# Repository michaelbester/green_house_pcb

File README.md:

This is the PCB design for the green house controller.  I used Kicad 6 to design the schematic and layout the board.

The uC pins connected to the fan #2, misc, and vent relays where incorrect.  
I jumpered these pins to unused pins that had output capability, but I can't get the outputs to go high.

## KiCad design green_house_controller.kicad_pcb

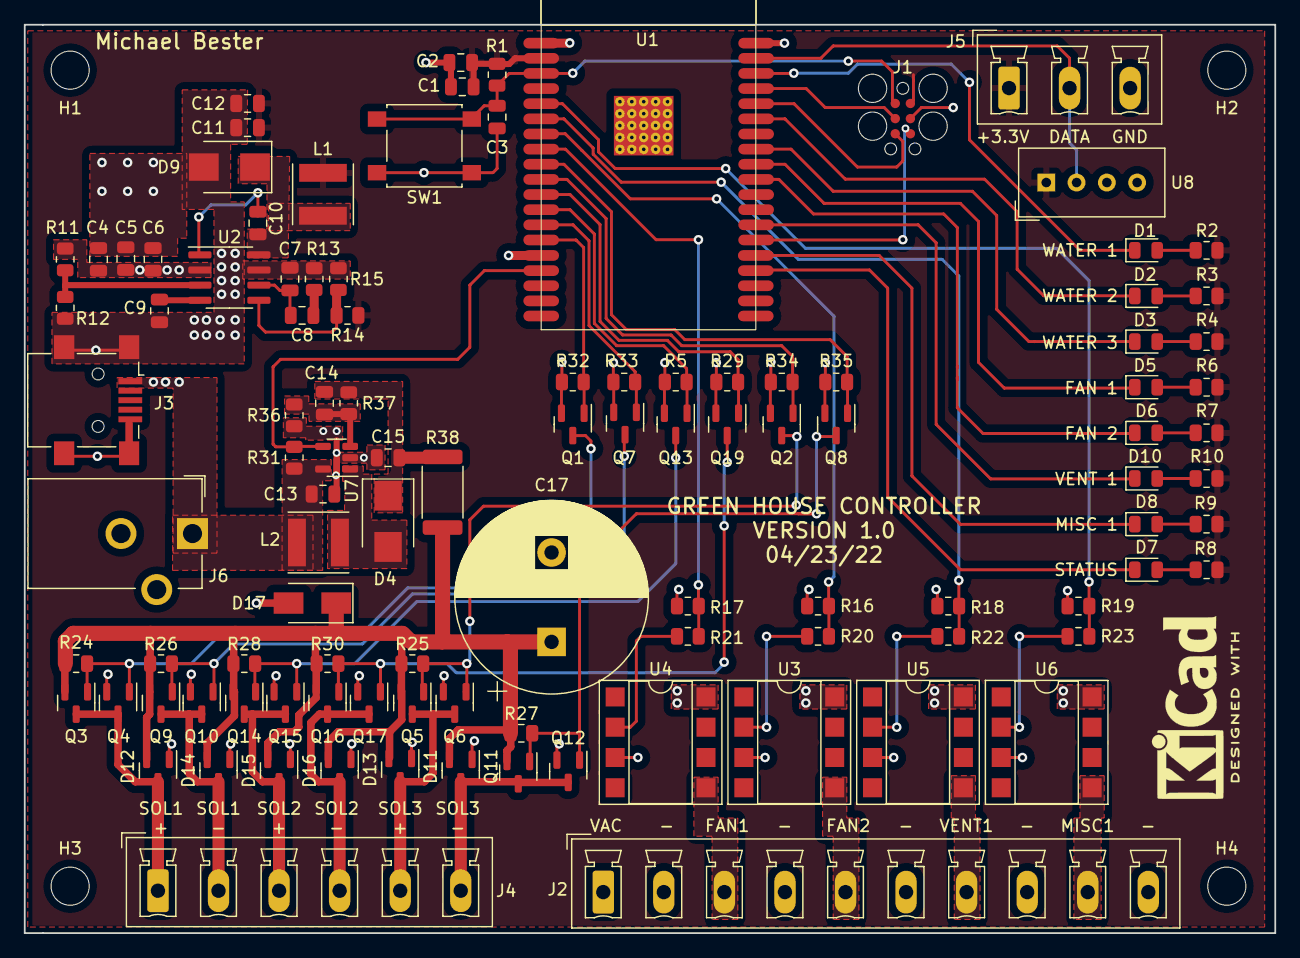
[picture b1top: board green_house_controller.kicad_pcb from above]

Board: 2 copper layers, 104.9 x 76.2 mm, 110 parts (0 on the bottom side), 68 nets.

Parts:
C1, C10: 0.1uF; C_0805_2012Metric
C2: 10uF; C_0805_2012Metric
C3: 1uF; C_0805_2012Metric
C4, C5, C15: 4.7uF; C_0805_2012Metric
C6: 0.01uF; C_0805_2012Metric
C7: 47pF; C_0805_2012Metric
C8: 1nF; C_0805_2012Metric
C9: 15nF; C_0805_2012Metric
C11, C12: 47uF; C_0805_2012Metric
C13: 2.2uF; C_0805_2012Metric
C14: 220pF; C_0805_2012Metric
C17: 2200uF; CP_Radial_D16.0mm_P7.50mm
D1: SOL_1; LED_0805_2012Metric
D2: SOL_2; LED_0805_2012Metric
D3: SOL_3; LED_0805_2012Metric
D4, D9: B240; D_SMB
D5: FAN; LED_0805_2012Metric
D6: VENT; LED_0805_2012Metric
D7: STATUS; LED_0805_2012Metric
D8: MISC_1; LED_0805_2012Metric
D10: VENT_1; LED_0805_2012Metric
D11, D12, D13, D14, D15, D16: BAT54S; SOT-23
D17: B140-E3; D_SMA
H1, H2, H3, H4: MountingHole; MountingHole_3.2mm_M3
J1: TC2030-IDC
J2: Screw_Terminal_01x10; PhoenixContact_MCV_1,5_10-G-5.08_1x10_P5.08mm_Vertical
J3: USB_B_Mini; USB_Mini-B_Lumberg_2486_01_Horizontal
J4: Screw_Terminal_01x06; PhoenixContact_MCV_1,5_6-G-5.08_1x06_P5.08mm_Vertical
J5: Screw_Terminal_01x03; PhoenixContact_MCV_1,5_3-G-5.08_1x03_P5.08mm_Vertical
J6: Barrel_Jack; BarrelJack_CUI_PJ-102AH_Horizontal
L1, L2: 10uH; L_Taiyo-Yuden_NR-50xx
Q1, Q2, Q7, Q8, Q13, Q19: 2N7002; SOT-23
Q3, Q5, Q9, Q11, Q14, Q16: DMP3068L; SOT-23
Q4, Q6, Q10, Q12, Q15, Q17: DMG3406L; SOT-23
R1, R12, R16, R17, R18, R19: 10K; R_0805_2012Metric
R2, R3, R4, R6, R7, R8, R9, R10: 330; R_0805_2012Metric
R5, R24, R25, R26, R27, R28, R29, R30, R32, R33, R34, R35, R36: 1K; R_0805_2012Metric
R11: 22K; R_0805_2012Metric
R13: 29.4K; R_0805_2012Metric
R14: 10.2K; R_0805_2012Metric
R15: 3.24K; R_0805_2012Metric
R20, R21, R22, R23: 200; R_0805_2012Metric
R31: 51K; R_0805_2012Metric
R37: 18.7K; R_0805_2012Metric
R38: 100; R_2512_6332Metric
SW1: SW_Push; SW_SPST_B3S-1000
U1: ESP32-WROVER
U2: TPS54231; SOIC-8_3.9x4.9mm_P1.27mm
U3, U4, U5, U6: TLP3825TP1_F; DIP-8_W7.62mm_SMDSocket_SmallPads
U7: LM2733XMF; SOT-23-5
U8: DHT11; Aosong_DHT11_5.5x12.0_P2.54mm

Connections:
+3V3: C1.1, C2.1, C11.1, C12.1, J1.2 (SWDIO), J5.1, L1.2, R1.1, R2.1, R3.1, R4.1, R6.1, R7.1, R8.1, R9.1, R10.1, R14.1, U1.2 (3V3), U8.1 (VCC)
+24V: C14.2, C15.1, D4.1 (K), R37.2, R38.1
+VDC: C17.1, D11.2, D12.2, D13.2, D14.2, D15.2, D16.2, D17.1 (K), Q3.2 (S), Q5.2 (S), Q9.2 (S), Q11.2 (S), Q14.2 (S), Q16.2 (S), R24.1, R25.1, R26.1, R27.1, R28.1, R30.1, R38.2
/microcontroller/BOOT_MODE: J1.6 (SWO), U1.25 (IO0)
/microcontroller/DHT11_DATA: J5.2, U1.37 (IO23), U8.2 (IO)
/microcontroller/EN_24V: R31.2, U1.16 (IO13), U7.4 (EN)
/microcontroller/ESP32_RX: J1.5 (GND), U1.34 (RXD0)
/microcontroller/ESP32_TX: J1.3 (NRESET), U1.35 (TXD0)
/microcontroller/FAN_1_CTRL: R17.1, R21.2, U1.8 (IO32_XTAL_32K_P)
/microcontroller/FAN_2_CTRL: R16.1, R20.2, U1.7 (IO35)
/microcontroller/LED_FAN_1: D5.1 (K), U1.30 (IO18)
/microcontroller/LED_FAN_2: D6.1 (K), U1.29 (IO5)
/microcontroller/LED_MISC_1: D8.1 (K), U1.24 (IO2)
/microcontroller/LED_SOL_1: D1.1 (K), U1.36 (IO22)
/microcontroller/LED_SOL_2: D2.1 (K), U1.33 (IO21)
/microcontroller/LED_SOL_3: D3.1 (K), U1.31 (IO19)
/microcontroller/LED_STATUS: D7.1 (K), U1.23 (IO15)
/microcontroller/LED_VENT_1: D10.1 (K), U1.26 (IO4)
/microcontroller/MISC_1_CTRL: R19.1, R23.2, U1.5 (SENSOR_VN_IO39)
/microcontroller/RESET: C3.1, J1.1 (VCC), R1.2, SW1.2, U1.3 (EN)
/microcontroller/SOL_1_CLOSE_CTRL: Q1.1 (G), R32.1, U1.14 (IO12)
/microcontroller/SOL_1_OPEN_CTRL: Q7.1 (G), R33.1, U1.13 (IO14)
/microcontroller/SOL_2_CLOSE_CTRL: Q13.1 (G), R5.1, U1.12 (IO27)
/microcontroller/SOL_2_OPEN_CTRL: Q19.1 (G), R29.1, U1.11 (IO26)
/microcontroller/SOL_3_CLOSE_CTRL: Q2.1 (G), R34.1, U1.10 (IO25)
/microcontroller/SOL_3_OPEN_CTRL: Q8.1 (G), R35.1, U1.9 (IO33_XTAL_32K_N)
/microcontroller/VENT_1_CTRL: R18.1, R22.2, U1.6 (IO34)
/power supply/VIN: C4.1, C5.1, C6.1, C13.1, J3.1 (VBUS), J6.1, L2.1, R11.1, R31.1, U2.2 (VIN), U7.5 (VIN)
/relay control/110VAC: J2.1, U3.8 (DRAIN), U4.8 (DRAIN), U5.8 (DRAIN), U6.8 (DRAIN)
/relay control/FAN_1_PWR: J2.3, U4.5 (DRAIN)
/relay control/FAN_2_PWR: J2.5, U3.5 (DRAIN)
/relay control/MISC_1_PWR: J2.9, U6.5 (DRAIN)
/relay control/VENT_1_PWR: J2.7, U5.5 (DRAIN)
/solenoid control/SOL_1_PWR+: D12.3, J4.1, Q3.3 (D), Q4.3 (D)
/solenoid control/SOL_1_PWR-: D14.3, J4.2, Q9.3 (D), Q10.3 (D)
/solenoid control/SOL_2_PWR+: D15.3, J4.3, Q14.3 (D), Q15.3 (D)
/solenoid control/SOL_2_PWR-: D16.3, J4.4, Q16.3 (D), Q17.3 (D)
/solenoid control/SOL_3_PWR+: D11.3, J4.5, Q5.3 (D), Q6.3 (D)
/solenoid control/SOL_3_PWR-: D13.3, J4.6, Q11.3 (D), Q12.3 (D)
Earth: J2.2, J2.4, J2.6, J2.8, J2.10
GND: C1.2, C2.2, C3.2, C4.2, C5.2, C6.2, C7.2, C9.2, C11.2, C12.2, C13.2, C15.2, C17.2, D9.2 (A), D11.1, D12.1, D13.1, D14.1, D15.1, D16.1, D17.2 (A), J1.4 (SWCLK), J3.5 (GND), J3.6 (Shield), J5.3, J6.2, Q1.2 (S), Q2.2 (S), Q4.2 (S), Q6.2 (S), Q7.2 (S), Q8.2 (S), Q10.2 (S), Q12.2 (S), Q13.2 (S), Q15.2 (S), Q17.2 (S), Q19.2 (S), R5.2, R12.2, R13.2, R15.2, R16.2, R17.2, R18.2, R19.2, R29.2, R32.2, R33.2, R34.2, R35.2, R36.1, SW1.1, U1.1 (GND), U1.15 (GND), U1.38 (GND), U1.39 (GND), U2.7 (GND), U3.3 (CATHODE), U4.3 (CATHODE), U5.3 (CATHODE), U6.3 (CATHODE), U7.2 (GND), U8.4 (GND)
unnamed: C7.1, C8.1, U2.6 (COMP)
unnamed: C8.2, R13.1
unnamed: C9.1, U2.4 (SS)
unnamed: C10.1, U2.1 (BOOT)
unnamed: C10.2, D9.1 (K), L1.1, U2.8 (PH)
unnamed: C14.1, R36.2, R37.1, U7.3 (FB)
unnamed: D1.2 (A), R2.2
unnamed: D2.2 (A), R3.2
unnamed: D3.2 (A), R4.2
unnamed: D4.2 (A), L2.2, U7.1 (SW)
unnamed: D5.2 (A), R6.2
unnamed: D6.2 (A), R7.2
unnamed: D7.2 (A), R8.2
unnamed: D8.2 (A), R9.2
unnamed: D10.2 (A), R10.2
unnamed: Q1.3 (D), Q3.1 (G), Q4.1 (G), R24.2
unnamed: Q2.3 (D), Q5.1 (G), Q6.1 (G), R25.2
unnamed: Q7.3 (D), Q9.1 (G), Q10.1 (G), R26.2
unnamed: Q8.3 (D), Q11.1 (G), Q12.1 (G), R27.2
unnamed: Q13.3 (D), Q14.1 (G), Q15.1 (G), R28.2
unnamed: Q16.1 (G), Q17.1 (G), Q19.3 (D), R30.2
unnamed: R11.2, R12.1, U2.3 (EN)
unnamed: R14.2, R15.1, U2.5 (FB)
unnamed: R20.1, U3.2 (ANODE)
unnamed: R21.1, U4.2 (ANODE)
unnamed: R22.1, U5.2 (ANODE)
unnamed: R23.1, U6.2 (ANODE)

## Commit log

2022-04-25 Initial commit.
2022-04-26 Added connector for temperature sensor. Started to route board.
2022-04-26 Added clamping diode for 24V net.
2022-04-26 Flipped top fets for solenoid controls so that the body diode was pointing the correction direction.
2022-04-27 Continued with layout.
2022-04-28 Finished layout for +24V regulator circuit.
2022-04-29 Finished initial layout. Zero DRC errors/warnings.
2022-04-29 Added DHT11 footprint. Updated feedback resistor values for regulator circuit. Created gerber and drill files for version 1.
2022-04-29 Fixed 3.3V net disconnection issue.
2022-05-04 Replaced relays with smd versions.
2025-01-25 Initial part placement on PCB
